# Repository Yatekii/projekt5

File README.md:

# projekt5
Analog Front End for an SDR

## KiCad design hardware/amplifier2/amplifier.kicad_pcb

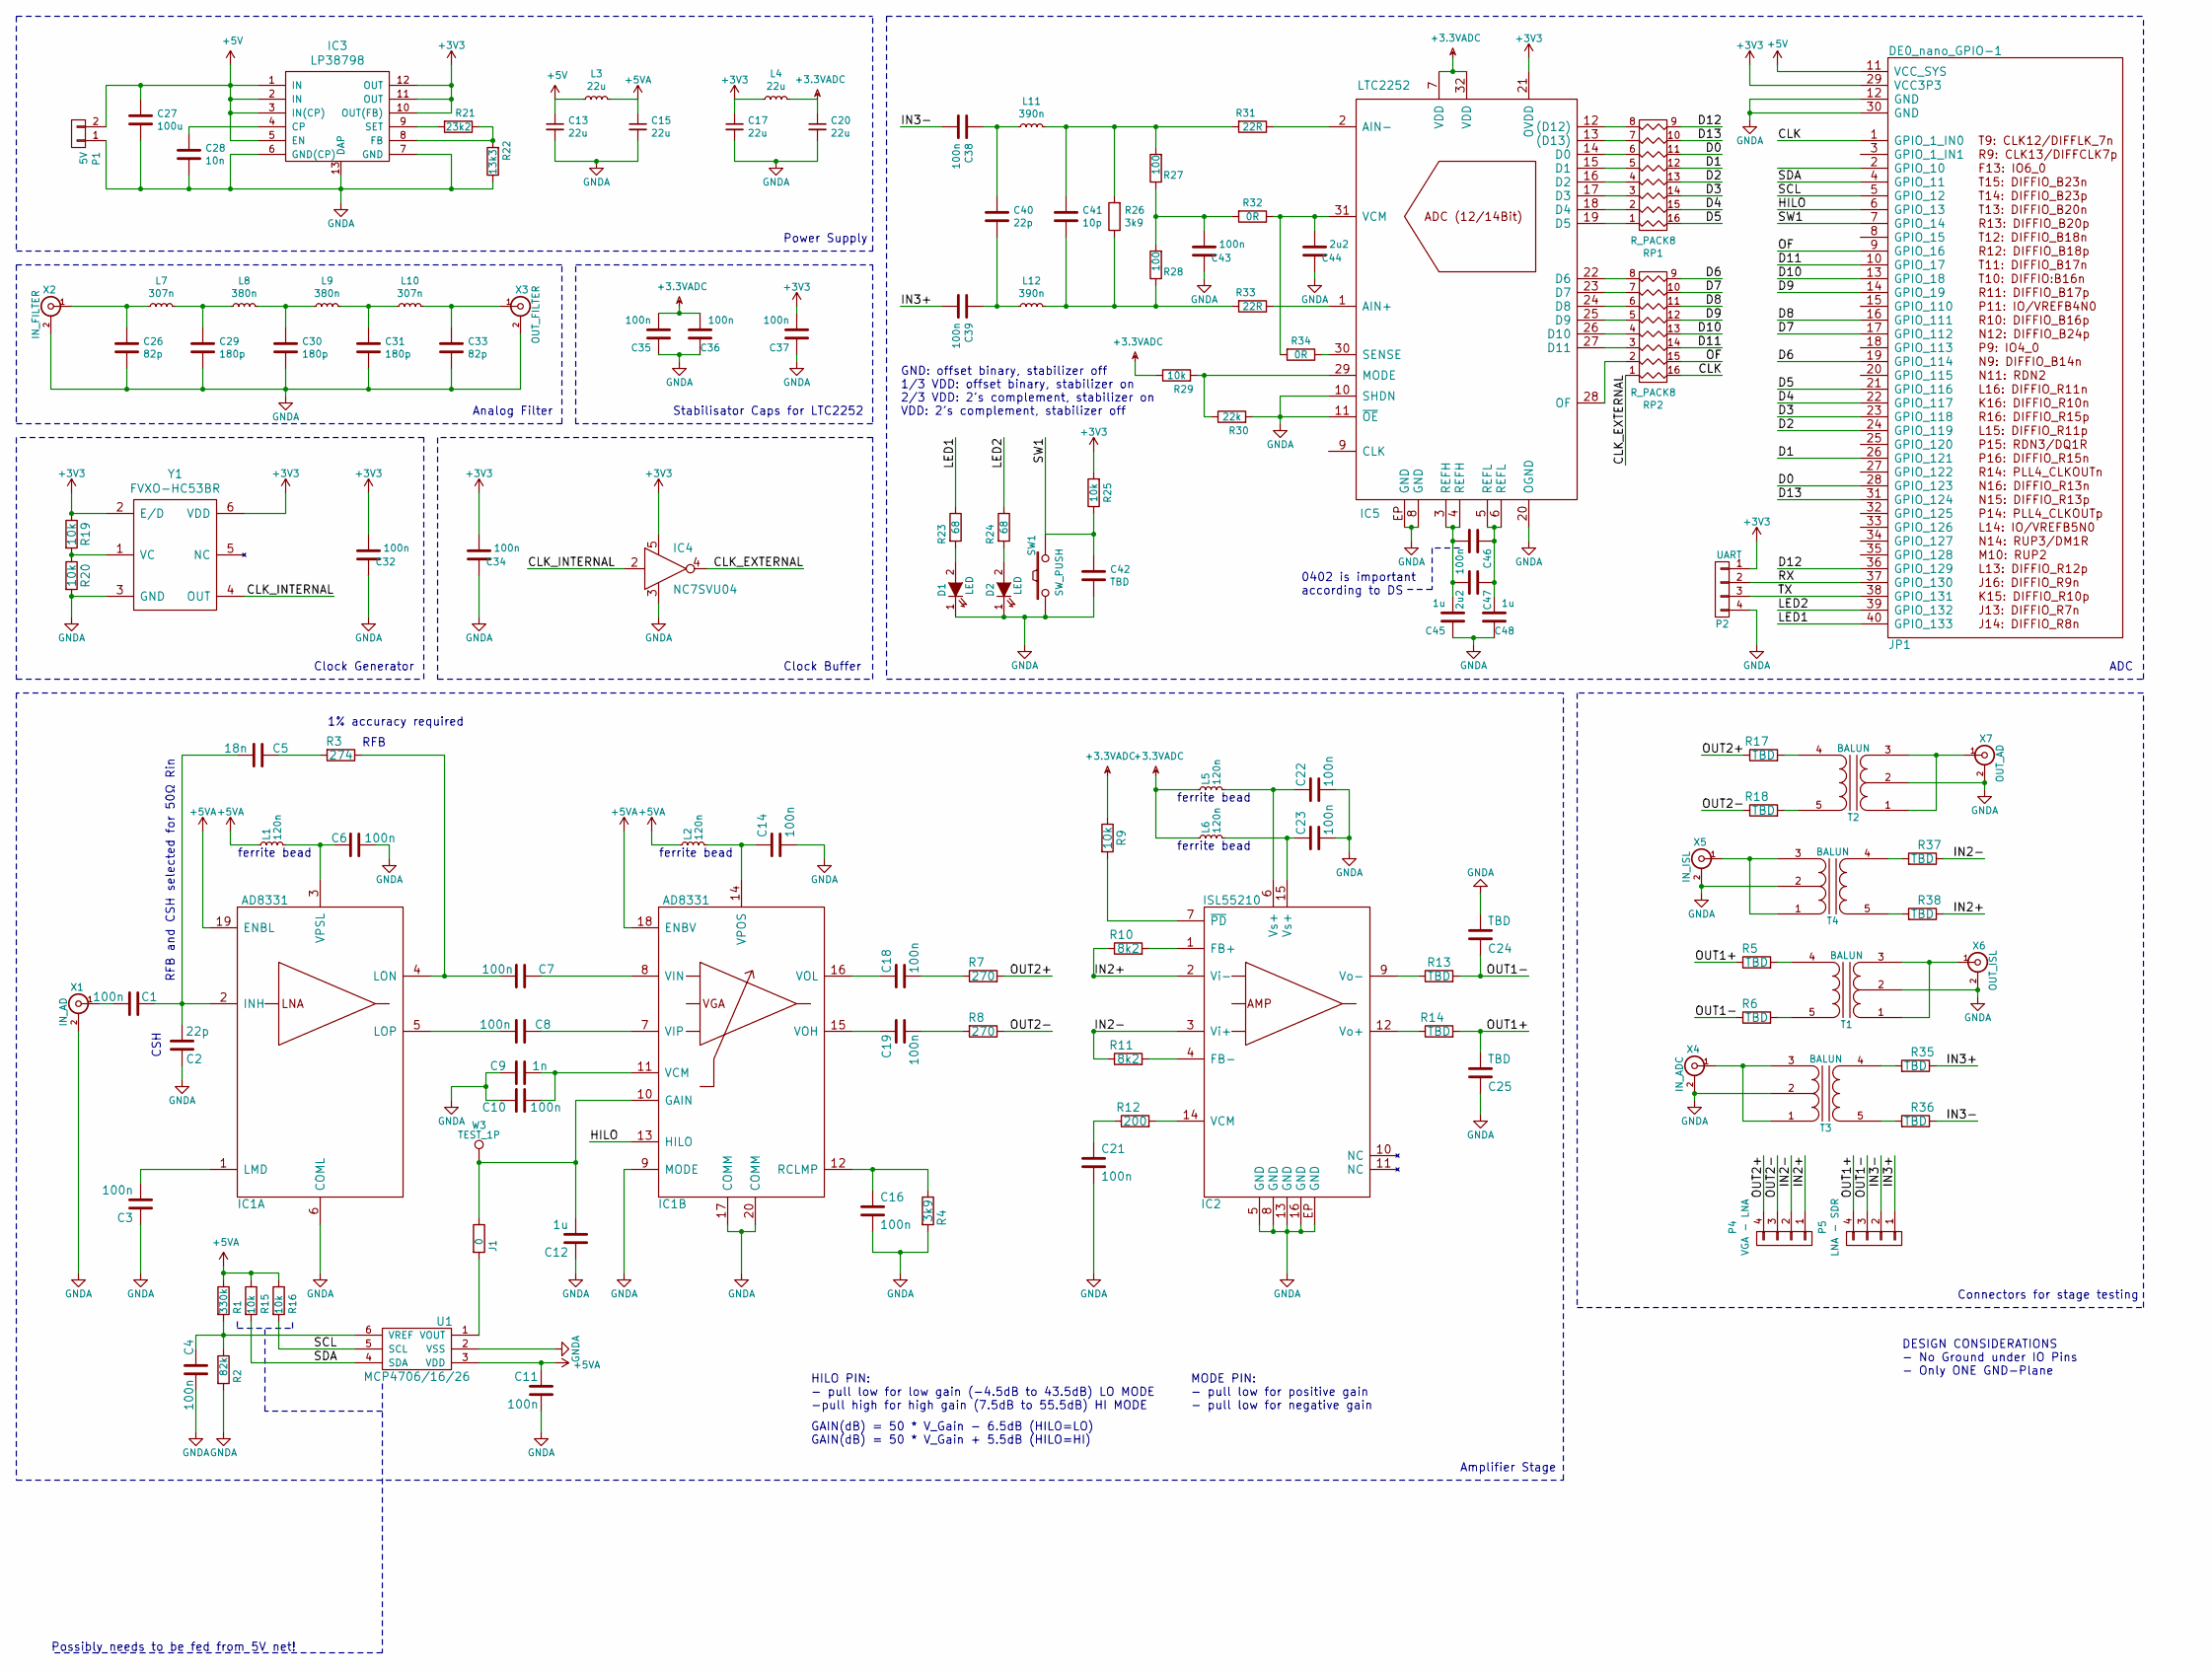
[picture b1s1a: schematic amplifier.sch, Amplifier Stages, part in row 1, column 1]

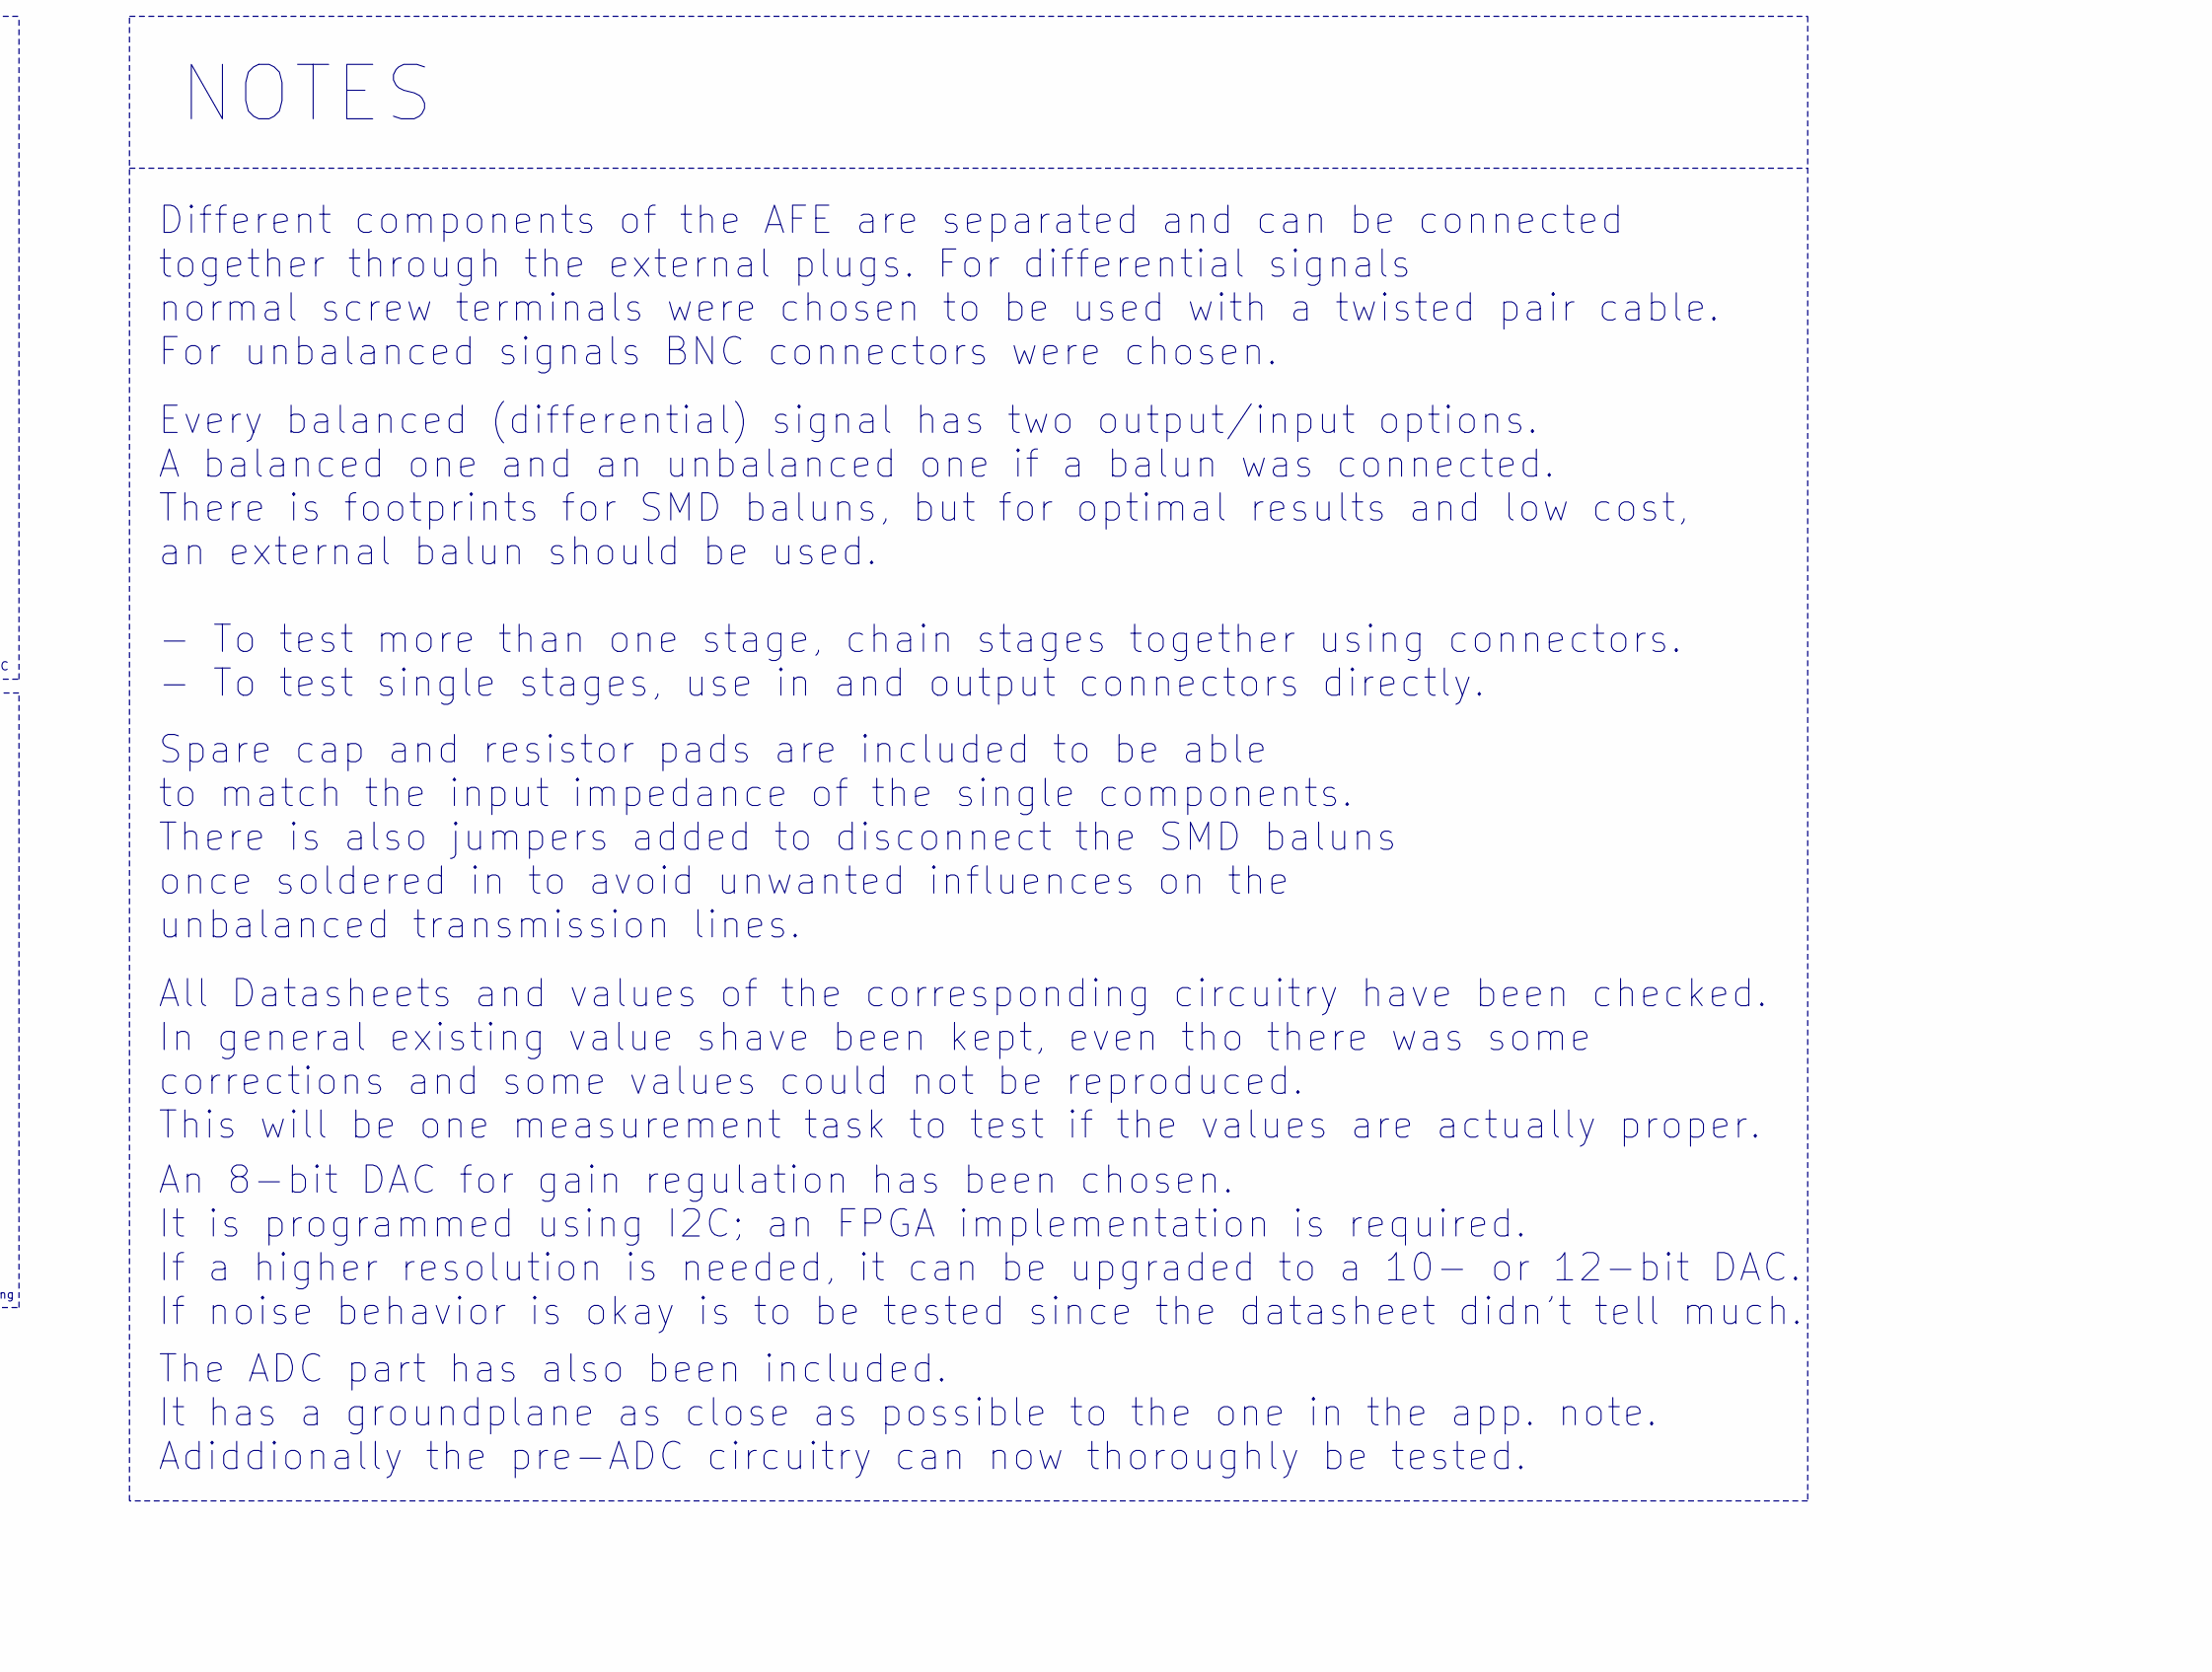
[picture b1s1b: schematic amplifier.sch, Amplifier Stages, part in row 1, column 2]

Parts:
C1, C3, C4, C6, C7, C8, C10, C11, C14, C16, C18, C19, C21, C22, C23, C32, C34, C35, C36, C37, C38, C39, C43: 100n; C_0603
C2, C40: 22p; C_0603
C5: 18n; C_0603
C9: 1n; C_0603
C12, C45, C48: 1u; C_0603
C13, C15, C17, C20: 22u; C_1210
C24, C25, C42: TBD; C_0603
C26, C33: 82p; C_0603
C27: 100u; C_1210
C28: 10n; C_0603
C29, C30, C31: 180p; C_0603
C41: 10p; C_0603
C44, C47: 2u2; C_0603
C46: 100n; C_0402
D1, D2: LED; LED_0603
IC1: AD8331; QSOP20
IC2: ISL55210; TQFN16
IC3: LP38798; WSON12
IC4: NC7SVU04; SOT353
IC5: LTC2252; QFN-32-1EP_5x5mm_Pitch0.5mm
J1: 0; R_0603
JP1: DE0_nano_GPIO-1; Pin_Header_Angled_2x20
L1, L2, L5, L6: 120n; R_0603
L3, L4: 22u; Choke_SMD_1206_Standard
L7, L10: 307n; Coil_132-XXSM_L_
L8, L9: 380n; Coil_132-XXSM_L_
L11, L12: 390n; 1008
P1: 5V; ED365-2
P2: UART; Molex_PicoBlade_53398-0471_04x1.25mm_Straight
P4: VGA - LNA; ED365-4
P5: LNA - SDR; ED365-4
R1: 330k; R_0603
R2: 82k; R_0603
R3: 274; R_0603
R4, R26: 3k9; R_0603
R5, R6, R13, R14, R17, R18, R35, R36, R37, R38: TBD; R_0603
R7, R8: 270; R_0603
R9, R15, R16, R19, R20, R25, R29: 10k; R_0603
R10, R11: 8k2; R_0603
R12: 200; R_0603
R21: 23k2; R_0603
R22: 13k3; R_0603
R23, R24: 68; R_0603
R27, R28: 100; R_0603
R30: 22k; R_0603
R31, R33: 22R; R_0603
R32, R34: 0R; R_0603
RP1, RP2: R_PACK8; 2406
SW1: SW_PUSH; SW_SPST_PTS645
T1, T2, T3, T4: BALUN; T4-1-KK81
U1: MCP4706/16/26; SOT-23-6
W3: TEST_1P; Test_Point_Keystone_5005-5009_Compact
X1: IN_AD; 1-1337543-0
X2: IN_FILTER; 1-1337543-0
X3: OUT_FILTER; 1-1337543-0
X4: IN_ADC; 1-1337543-0
X5: IN_ISL; 1-1337543-0
X6: OUT_ISL; 1-1337543-0
X7: OUT_AD; 1-1337543-0
Y1: FVXO-HC53BR; OSC_631-1265-1-ND

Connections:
+3.3VADC: C20.1, C35.2, C36.2, IC5.7 (VDD), IC5.32 (VDD), L4.2, L5.1, L6.1, R9.1, R29.1
+3V3: C17.1, C32.2, C34.2, C37.2, IC3.10 (OUT(FB)), IC3.11 (OUT), IC3.12 (OUT), IC4.5 (VCC), IC5.21 (OVDD), JP1.29 (VCC3P3), L4.1, P2.1, R19.1, R25.2, Y1.2 (E/D), Y1.6 (VDD)
+5V: C13.1, C27.1, IC3.1 (IN), IC3.2 (IN), IC3.3 (IN(CP)), IC3.5 (EN), JP1.11 (VCC_SYS), L3.1, P1.2
+5VA: C11.1, C15.1, IC1.18 (ENBV), IC1.19 (ENBL), L1.1, L2.1, L3.2, R1.1, R15.1, R16.1, U1.3 (VDD)
/CLK: JP1.1 (GPIO_1_IN0), RP2.16 (R1)
/CLK_EXTERNAL: IC4.4 (Y), RP2.1
/CLK_INTERNAL: IC4.2 (A), Y1.4 (OUT)
/D0: JP1.28 (GPIO_123), RP1.11 (R6)
/D1: JP1.26 (GPIO_121), RP1.12 (R5)
/D2: JP1.24 (GPIO_119), RP1.13 (R4)
/D3: JP1.23 (GPIO_118), RP1.14 (R3)
/D4: JP1.22 (GPIO_117), RP1.15 (R2)
/D5: JP1.21 (GPIO_116), RP1.16 (R1)
/D6: JP1.19 (GPIO_114), RP2.9 (R8)
/D7: JP1.17 (GPIO_112), RP2.10 (R7)
/D8: JP1.16 (GPIO_111), RP2.11 (R6)
/D9: JP1.14 (GPIO_19), RP2.12 (R5)
/D10: JP1.13 (GPIO_18), RP2.13 (R4)
/D11: JP1.10 (GPIO_17), RP2.14 (R3)
/D12: JP1.36 (GPIO_129), RP1.9 (R8)
/D13: JP1.31 (GPIO_124), RP1.10 (R7)
/HILO: IC1.13 (HILO), JP1.6 (GPIO_13)
/IN2+: IC2.2 (Vi-), P4.1, R10.1, R38.1
/IN2-: IC2.3 (Vi+), P4.2, R11.1, R37.1
/IN3+: C39.2, P5.1, R35.1
/IN3-: C38.2, P5.2, R36.1
/LED1: JP1.40 (GPIO_133), R23.1
/LED2: JP1.39 (GPIO_132), R24.1
/OF: JP1.9 (GPIO_16), RP2.15 (R2)
/OUT1+: C25.1, P5.4, R5.1, R14.2
/OUT1-: C24.2, P5.3, R6.1, R13.2
/OUT2+: P4.4, R7.2, R17.1
/OUT2-: P4.3, R8.1, R18.1
/RX: JP1.37 (GPIO_130), P2.2
/SCL: JP1.5 (GPIO_12), R16.2, U1.5 (SCL)
/SDA: JP1.4 (GPIO_11), R15.2, U1.4 (SDA)
/SW1: C42.1, JP1.7 (GPIO_14), R25.1, SW1.2
/TX: JP1.38 (GPIO_131), P2.3
GNDA: C2.1, C3.1, C4.2, C6.2, C9.1, C10.1, C11.2, C12.1, C13.2, C14.2, C15.2, C16.2, C17.2, C20.2, C21.2, C22.1, C23.1, C24.1, C25.2, C26.2, C27.2, C28.2, C29.2, C30.2, C31.2, C32.1, C33.2, C34.1, C35.1, C36.1, C37.1, C42.2, C43.1, C44.1, C45.1, C48.1, D1.1 (K), D2.1 (K), IC1.6 (COML), IC1.9 (MODE), IC1.17 (COMM), IC1.20 (COMM), IC2.5 (GND), IC2.8 (GND), IC2.13 (GND), IC2.16 (GND), IC2.EP (GND), IC3.6 (GND(CP)), IC3.7 (GND), IC3.13 (DAP), IC4.3 (GND), IC5.8 (GND), IC5.10 (SHDN), IC5.11 (~OE), IC5.20 (OGND), IC5.EP (GND), JP1.12 (GND), JP1.30 (GND), P1.1, P2.4, R2.2, R4.2, R20.2, R22.1, R30.2, SW1.1, T1.2 (PM), T2.2 (PM), T3.2 (PM), T4.2 (PM), U1.2 (VSS), X1.2 (Ext), X2.2 (Ext), X3.2 (Ext), X4.2 (Ext), X5.2 (Ext), X6.2 (Ext), X7.2 (Ext), Y1.3 (GND)
unnamed: C1.1, C2.2, C5.2, IC1.2 (INH)
unnamed: C1.2, X1.1 (In)
unnamed: C3.2, IC1.1 (LMD)
unnamed: C4.1, R1.2, R2.1, U1.6 (VREF)
unnamed: C5.1, R3.2
unnamed: C6.1, IC1.3 (VPSL), L1.2
unnamed: C7.1, IC1.4 (LON), R3.1
unnamed: C7.2, IC1.8 (VIN)
unnamed: C8.1, IC1.7 (VIP)
unnamed: C8.2, IC1.5 (LOP)
unnamed: C9.2, C10.2, IC1.11 (VCM)
unnamed: C12.2, IC1.10 (GAIN), J1.1, W3.1
unnamed: C14.1, IC1.14 (VPOS), L2.2
unnamed: C16.1, IC1.12 (RCLMP), R4.1
unnamed: C18.1, IC1.16 (VOL)
unnamed: C18.2, R7.1
unnamed: C19.1, IC1.15 (VOH)
unnamed: C19.2, R8.2
unnamed: C21.1, R12.1
unnamed: C22.2, IC2.6 (Vs+), L5.2
unnamed: C23.2, IC2.15 (Vs+), L6.2
unnamed: C26.1, L7.1, X2.1 (In)
unnamed: C28.1, IC3.4 (CP)
unnamed: C29.1, L7.2, L8.1
unnamed: C30.1, L8.2, L9.1
unnamed: C31.1, L9.2, L10.1
unnamed: C33.1, L10.2, X3.1 (In)
unnamed: C38.1, C40.1, L11.1
unnamed: C39.1, C40.2, L12.1
unnamed: C41.1, L11.2, R26.2, R27.2, R31.2
unnamed: C41.2, L12.2, R26.1, R28.1, R33.2
unnamed: C43.2, R27.1, R28.2, R32.2
unnamed: C44.2, IC5.31 (VCM), R32.1, R34.2
unnamed: C45.2, C46.2, C47.2, IC5.3 (REFH), IC5.4 (REFH)
unnamed: C46.1, C47.1, C48.2, IC5.5 (REFL), IC5.6 (REFL)
unnamed: D1.2 (A), R23.2
unnamed: D2.2 (A), R24.2
unnamed: IC2.1 (FB+), R10.2
unnamed: IC2.4 (FB-), R11.2
unnamed: IC2.7 (~PD), R9.2
unnamed: IC2.9 (Vo-), R13.1
unnamed: IC2.12 (Vo+), R14.1
unnamed: IC2.14 (VCM), R12.2
unnamed: IC3.8 (FB), R21.1, R22.2
unnamed: IC3.9 (SET), R21.2
unnamed: IC5.1 (AIN+), R33.1
unnamed: IC5.2 (AIN-), R31.1
unnamed: IC5.12 ((D12)), RP1.8
unnamed: IC5.13 ((D13)), RP1.7
unnamed: IC5.14 (D0), RP1.6
unnamed: IC5.15 (D1), RP1.5
unnamed: IC5.16 (D2), RP1.4
unnamed: IC5.17 (D3), RP1.3
unnamed: IC5.18 (D4), RP1.2
unnamed: IC5.19 (D5), RP1.1
unnamed: IC5.22 (D6), RP2.8
unnamed: IC5.23 (D7), RP2.7
unnamed: IC5.24 (D8), RP2.6
unnamed: IC5.25 (D9), RP2.5
unnamed: IC5.26 (D10), RP2.4
unnamed: IC5.27 (D11), RP2.3
unnamed: IC5.28 (OF), RP2.2
unnamed: IC5.29 (MODE), R29.2, R30.1
unnamed: IC5.30 (SENSE), R34.1
unnamed: J1.2, U1.1 (VOUT)
unnamed: R5.2, T1.4 (S1)
unnamed: R6.2, T1.5 (S2)
unnamed: R17.2, T2.4 (S1)
unnamed: R18.2, T2.5 (S2)
unnamed: R19.2, R20.1, Y1.1 (VC)
unnamed: R35.2, T3.4 (S1)
unnamed: R36.2, T3.5 (S2)
unnamed: R37.2, T4.4 (S1)
unnamed: R38.2, T4.5 (S2)
unnamed: T1.1 (PR1), T1.3 (PR2), X6.1 (In)
unnamed: T2.1 (PR1), T2.3 (PR2), X7.1 (In)
unnamed: T3.1 (PR1), T3.3 (PR2), X4.1 (In)
unnamed: T4.1 (PR1), T4.3 (PR2), X5.1 (In)

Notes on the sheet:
MODE PIN: - pull low for positive gain - pull low for negative gain
HILO PIN: - pull low for low gain (-4.5dB to 43.5dB) LO MODE -pull high for high gain (7.5dB to 55.5dB) HI MODE
GAIN(dB) = 50 * V_Gain - 6.5dB (HILO=LO) GAIN(dB) = 50 * V_Gain + 5.5dB (HILO=HI)
1% accuracy required
RFB and CSH selected for 50Ω Rin
CSH
RFB
DESIGN CONSIDERATIONS - No Ground under IO Pins - Only ONE GND-Plane
ferrite bead
Power Supply
Amplifier Stage
Analog Filter
Clock Generator
Clock Buffer
0402 is important according to DS
Stabilisator Caps for LTC2252
GND: offset binary, stabilizer off 1/3 VDD: offset binary, stabilizer on 2/3 VDD: 2’s complement, stabilizer on VDD: 2’s complement, stabilizer off
Connectors for stage testing
ADC
Different components of the AFE are separated and can be connected together through the external plugs. For differential signals normal screw terminals were chosen to be used with a twisted pair cable. For unbalanced signals BNC connectors were chosen.
Every balanced (differential) signal has two output/input options. A balanced one and an unbalanced one if a balun was connected. There is footprints for SMD baluns, but for optimal results and low cost, an external balun should be used. - To test more than one stage, chain stages together using co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
Spare cap and resistor pads are included to be able to match the input impedance of the single components. There is also jumpers added to disconnect the SMD baluns once soldered in to avoid unwanted influences on the unbalanced transmission lines.
NOTES
All Datasheets and values of the corresponding circuitry have been checked. In general existing value shave been kept, even tho there was some corrections and some values could not be reproduced. This will be one measurement task to test if the values are actually proper.
An 8-bit DAC for gain regulation has been chosen. It is programmed using I2C; an FPGA implementation is required. If a higher resolution is needed, it can be upgraded to a 10- or 12-bit DAC. If noise behavior is okay is to be tested since the datasheet didn’t tell much.
The ADC part has also been included. It has a groundplane as close as possible to the one in the app. note. Adiddionally the pre-ADC circuitry can now thoroughly be tested.
Possibly needs to be fed from 5V net!

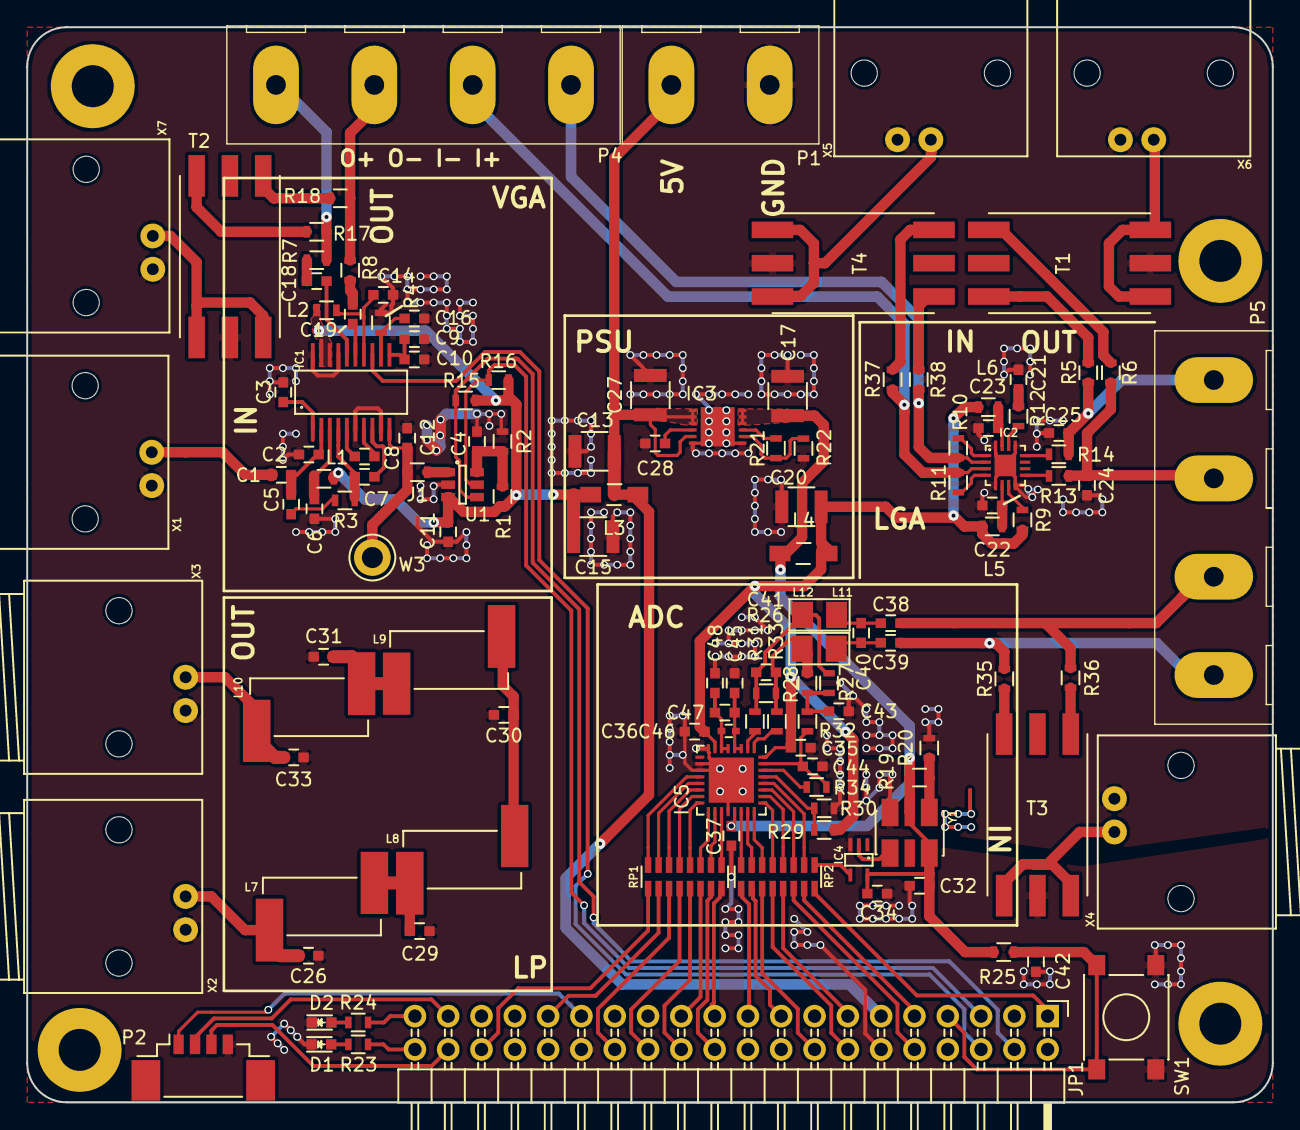
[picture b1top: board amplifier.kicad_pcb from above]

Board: 2 copper layers, 95.0 x 82.0 mm, 132 parts (0 on the bottom side), 117 nets.

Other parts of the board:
M1, M2, M3, M4: MountingHole_3.2mm_M3_Pad

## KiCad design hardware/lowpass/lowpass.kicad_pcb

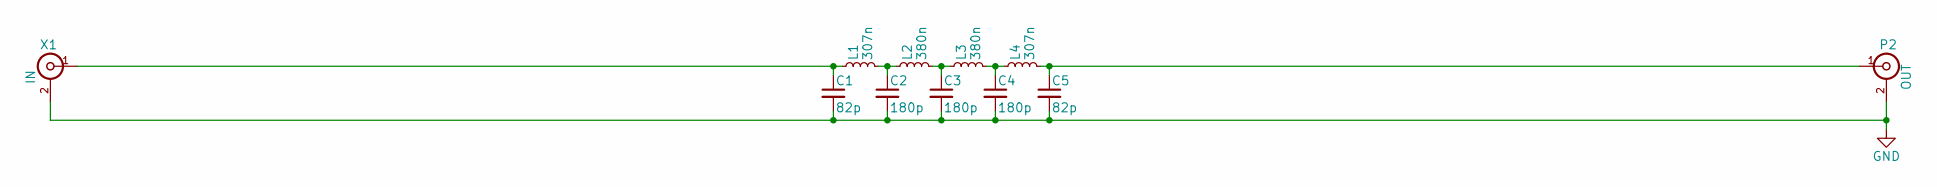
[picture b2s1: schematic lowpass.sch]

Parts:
C1, C5: 82p; C_0603_HandSoldering
C2, C3, C4: 180p; C_0603_HandSoldering
L1, L4: 307n
L2, L3: 380n
P2: OUT; 1-1337543-0
X1: IN; 1-1337543-0

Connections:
GND: C1.2, C2.2, C3.2, C4.2, C5.2, P2.2 (Ext), X1.2 (Ext)
unnamed: C1.1, L1.1, X1.1 (In)
unnamed: C2.1, L1.2, L2.1
unnamed: C3.1, L2.2, L3.1
unnamed: C4.1, L3.2, L4.1
unnamed: C5.1, L4.2, P2.1 (In)

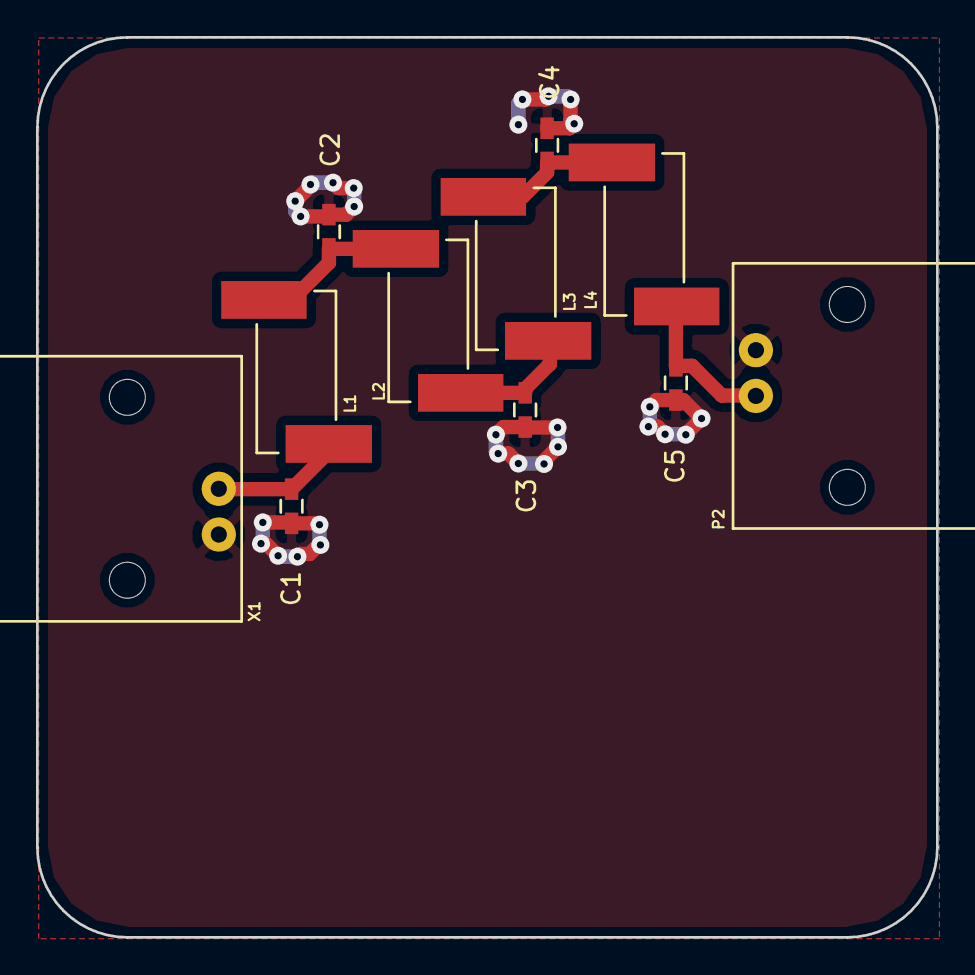
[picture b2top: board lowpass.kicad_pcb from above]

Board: 2 copper layers, 50.0 x 50.0 mm, 11 parts (0 on the bottom side), 6 nets.

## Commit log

2016-10-10 added template for kicad
2016-10-10 added rough time estimate; added datasheets
2016-10-11 Added datasheets for the various ICs
2016-10-15 Amp schema done
2016-10-15 Worked on amp schema; nearly done; ISL55210 needs review as well as output termination
2016-10-15 schema done for now; needs some minor changes; routing done for this schema
2016-10-18 Added lowpass simulation and schematic
2016-10-19 first version of filter layout
2016-10-27 amp done
2016-10-27 I failed
2016-10-27 Amp PCB completely done with power taps and baluns
2016-10-27 Fixed long traces in lowpass
2016-10-28 Added first version of powersupply schematic including datasheet
2016-11-10 wip noah
2016-11-10 joined all schemas; added ADC stage; needs footprint assignments and layout
2016-11-10 rerouting nearly done; added remaining footprints
2016-11-10 last state; minor changes still to do; powersupply missing; outline missing
2016-11-10 all routing but PSU done; maybe schema needs nicer annotations
2016-11-11 Renamed management files
2016-11-12 Updated and placed LDO, added wip bom. routing is wip
2016-11-12 Fixed the mess caused by rescue libraries
2016-11-12 Routed LDO, updated LED resistors, added resistor part numbers
2016-11-13 everything done routing; removed obsolete testpins; needs groundplane checks and stitchings; needs mounting holes; maybe elaborate in schema
2016-11-13 checked groundplane; added ground viastitching where necessary; added slits in groundplane where necessary; added mounting holes; adjusted silkscreen; adjusted board outline
2016-11-13 updated bom to fit
2016-11-13 styled bom
2016-11-13 Added notes to schematic explaining some of the features; Adjusted dimension markers of the board
2016-11-18 minor fixes mr. hufschmid mentioned
2016-11-28 Added notes from discussion with advisor
2016-11-29 Duplicated amp schematics for version1 so version2 can be edited already; added jupyter nb for measuring and evaluation; added pdf for bom; added arduino software to speak to dac
2016-12-01 added smith charts explained; added new measurements & calcs; added script for arduino due
2016-12-15 added measurements to date and script to access the labsupply
2016-12-15 measurement script now disables output after KeyboardInterrupt or normal termination
2016-12-15 Added basic network analyzer commands in python
2016-12-15 added scaffolding for guided measuring
2016-12-15 added all measurementsa
2016-12-15 fixed gitignore
2016-12-15 cleanup unused py module
2016-12-15 fixed syntax of nwa commands
2016-12-15 added calibration routines (untested)
2016-12-15 Automatic loading and storing of calibrations
2016-12-15 Added scripting guide and psu theory
2016-12-15 Made classes for measurement devices
2016-12-16 VNA should now do oneshot measurement
2016-12-16 Implemented power setup and single shot; untested
2016-12-16 Configuring works thus far except for calibration storing 'Invalid separator' error on vna ...
2016-12-16 ignored __pycache__, added csv to lfs, made measurement scripts work
2016-12-16 added measurement data from 2016-12-16
2016-12-17 Calcs on first measurements
2016-12-19 measurement script now supports specifying a measurement location; also fixed the bug with the fienames lacking an 0; measured some stuff with higher resolution
2016-12-19 changed broken filenames
2016-12-22 Measurements
2016-12-22 Prepared script for long term measurement
2016-12-23 cleanup and addition of Pretty- files
2017-01-12 scaffolding for latex report
2017-01-12 started article about afe; tried tikz; life sux
2017-01-13 worked on AFE part
2017-01-13 Blockdiagram for AFE done for now
2017-01-13 ground layout img done
2017-01-14 added missing pd
2017-01-15 work on mesurements section; drawn circuit with tikz yay!
2017-01-15 added calcs for terminator
2017-01-15 Paragraph about LP38798
2017-01-15 added plots of broken and whole AFE
2017-01-15 nearly done documenting measurements
2017-01-17 minor changes to measurements
2017-01-17 measurements part of report done
2017-01-17 fixed citing and did some cleanup of warnings
2017-01-17 described measuring devices
2017-01-18 Remove borked files
2017-01-18 Re-add files, hopefully fixing them
2017-01-18 Add some beta text
2017-01-18 measured a ton of the fixed PCB
2017-01-18 Added newest plots for last measurements
2017-01-18 UTF8 in main.tex, add basic abstract
2017-01-18 added schema
2017-01-18 Messungen almost done
2017-01-19 Reworked parts of afe, added supply chapter and ldo graphics
2017-01-19 sync main.pdf because lfs is being a little shit
2017-01-19 Rebuilt main pdf
2017-01-19 beautified ALL plots and added proper captions and labels
2017-01-19 beautified and corrected bom; added aufgabenstellung; added both to report
2017-01-19 track pifilter sim
2017-01-19 beautified projektplan; added it to report
2017-01-19 fixed wrong footprint
2017-01-19 Track remaining ltspice sim files and result from sim
2017-01-19 added some refs and list of figures; beautified some figures
2017-01-19 fixed wrong numbering on filter stuff; plotted filter measurements/sim
2017-01-19 minor fix on lowpass figure
2017-01-19 Rename motivation to einleitung, wrote einleitung
2017-01-19 sync main.pdf
2017-01-19 Rebuild pdf and cite previous pdf
2017-01-19 Created filter section and included power filter
2017-01-19 Some filter text
2017-01-19 added resultate & diskussion
2017-01-19 one more citation ...
2017-01-20 tikzed AFE filter
2017-01-20 fixed AFE graphic
2017-01-20 fixed AFE graphic 2
2017-01-20 Added problems with pre-existing system
2017-01-20 added adc and fpga to blockfiagram
2017-01-20 added comment to fixed errors
2017-01-20 appendix toc
2017-01-20 pifilter plot added
2017-01-20 tikzed pi filter
2017-01-20 proof read afe.tex
2017-01-20 fixed minor stuff in abstract
2017-01-20 update with new graphics, small changes in filter
2017-01-20 split filter chapter
2017-01-20 fixed typos; weirdo deutscheru; etc
2017-01-20 proof read messungen
2017-01-20 proof read resultate
2017-01-20 done proof reading
2017-01-20 last change from noahs side :P
2017-01-20 messungen spelling and small word changes
2017-01-20 personal reflection
2017-01-20 Small grammar fixes, removed hyperlative, corrected page/graphics flow
2017-01-20 fial compile
